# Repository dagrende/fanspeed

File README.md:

# fanspeed
pwm fan speed controller based on digispark-tiny85 and a quadrature encoder

I use a large PC fan to improve the ventilation around my 3d printer. It is 12V 1.3A and uses a 4 pin connector.

This is the project I used to learn to make my own PCBs and 3D printed cases.

## Firmware

The USB programmable Digispark takes some seconds to start. The fan spins up to fullsped then, and after that the encoder axis can be used to adjust speed. Left to do in the progam is to save the last used speed in EEPROM so that you don't have to tune the speed on each start.

## Components

The controller is a simple arduino with a atmel tiny85 processor.

A quadratur pulse encoder is used to adjust speed.

(for example https://www.ebay.com/p/3pcs-6mm-D-Shaft-18-Position-360-Degree-Rotary-Encoder-W-Push-Button-Ed/1749478696?_trksid=p2349526.c100534.m4207&_trkparms=aid%3D666006%26algo%3DPRP.MBE%26ao%3D1%26asc%3D20151029144032%26meid%3D657eb44e0d4b42509ba5e2342422b42b%26pid%3D100534%26rk%3D2%26rkt%3D4%26&rt=nc)

## power jack

I use a 1.3mm pin 3.5mm barrel connector. For example https://www.amazon.com/10Pcs-1-3x3-5mm-Female-Connector-Socket/dp/B00JR5HVA6.

## PCB

I use 0.4mm one sided PCB laminate.

The mounted PCB

Eagle Cad files are in board folder.

The PCB cad output

## Case

I use https://openjscad.org to create a 3d printable case.

### CAD model

### Live model (works in Chrome and Firefox)

https://openjscad.org/#https://raw.githubusercontent.com/dagrende/fanspeed/master/case/fanspeed-case.jscad

### 3D printed case

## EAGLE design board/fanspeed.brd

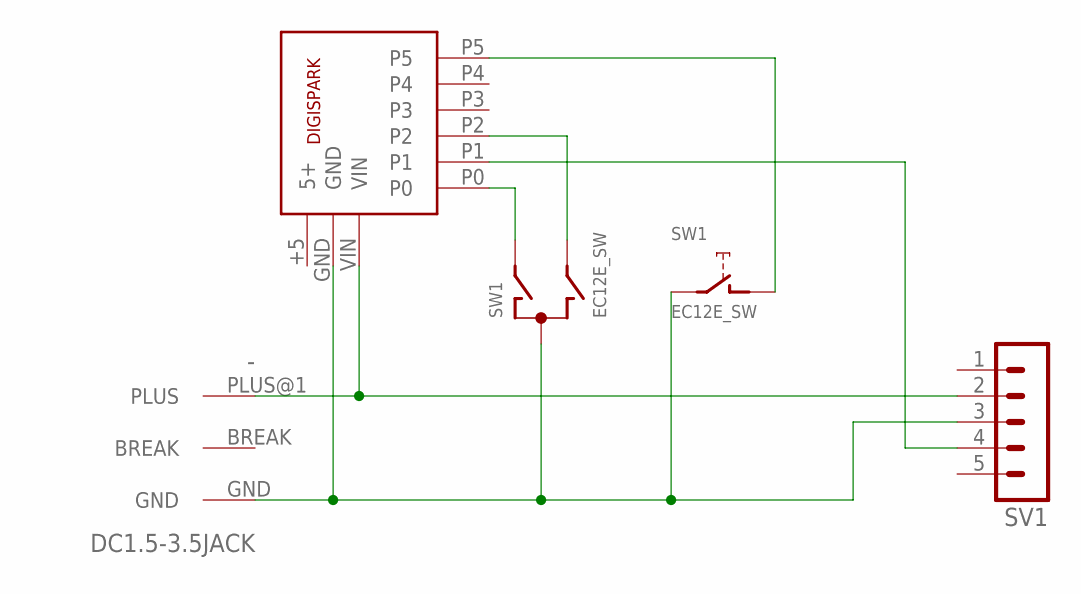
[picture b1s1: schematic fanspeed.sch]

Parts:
-: DC1.5-3.5JACK
SV1: MA05-1
SW1: EC12E_SW; ALPS_EC12E_SW
U1: DIGISPARK; DISPARK-BOARD

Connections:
GND: -.GND, SV1.3, SW1.C, SW1.E (2), U1.GND
unnamed: SW1.D (1), U1.P5
unnamed: SW1.B, U1.P2
unnamed: SV1.4, U1.P1
unnamed: SW1.A, U1.P0
unnamed: -.PLUS@1 (PLUS), SV1.2, U1.VIN

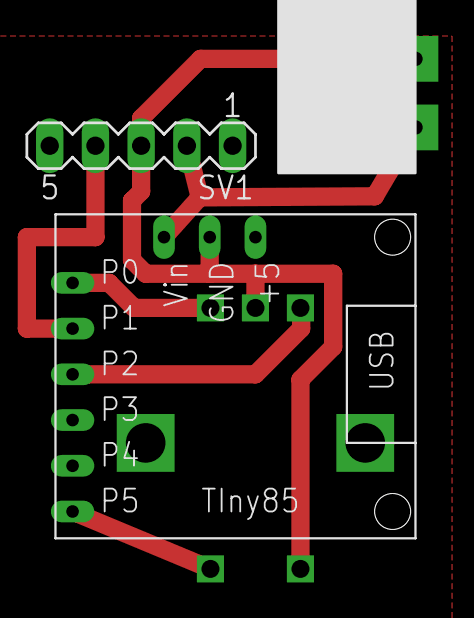
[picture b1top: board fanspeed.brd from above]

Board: 2 copper layers, 4 parts (1 on the bottom side), 6 nets.

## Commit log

2017-06-28 initial
2017-06-28 added docs
2017-06-28 cropped encoder image
2017-06-29 added module schematics
2017-07-09 added board eagle files, and replaced imported encoder with my own implementation
2017-07-09 restructured the code
2017-07-10 added case cad for 3d print
2017-07-12 moved and enlarged encoder axis hole in case
2017-07-12 added more doc pics
2017-07-13 more doc pics
2017-07-13 added some ebay links to docs
2017-07-15 created solder mask pdf
